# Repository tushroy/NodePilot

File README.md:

# NodePilot – CM108-Based AllStarLink Radio Interface  
NodePilot is a compact, reliable, and isolated **AllStarLink radio interface** based on the CM108 audio USB chipset by **S21TIP**.

This project was designed for both personal use and small-scale production, with a focus on audio quality, RF robustness, and hardware protection.

Channel Driver to used with ASL3: Simpleusb

The complete KiCad schematic, PCB (Work-in-progress), and design files are publicly available under the **CC-BY-SA-4.0** license.

Notes: If you are using buck converters to power Raspberry Pi boards, make sure the switching frequency is greater than 1 MHz for clean audio interfacing. Low-cost converters are often a significant source of RFI, although this circuit can eliminate most of it.

---

## 🔧 Features

✔️ CM108 Frontend Protection  
✔️ Full Audio Isolation  
✔️ Compact & Modular  
✔️ Open Hardware  

---

## 𖤓 Schematic

---

## 📐 PCB

---

---

## 📜 License

This project is released under the **Creative Commons Attribution-ShareAlike 4.0 International (CC-BY-SA-4.0)** license.  
You are free to remix, adapt, and build upon the design, even commercially, as long as you credit the author and share derivative works under the same license.

---

## 📡 Author  
**Tushar Roy – S21TIP**

If you improve the design or build your own version, feel free to open an Issue or Pull Request!

---

## 🌐 Links

### 🔗 QRZ Page  
https://www.qrz.com/db/S21TIP

### 🔗 Radiosanda FB Page  
https://www.facebook.com/share/1FPaPZSuz1/

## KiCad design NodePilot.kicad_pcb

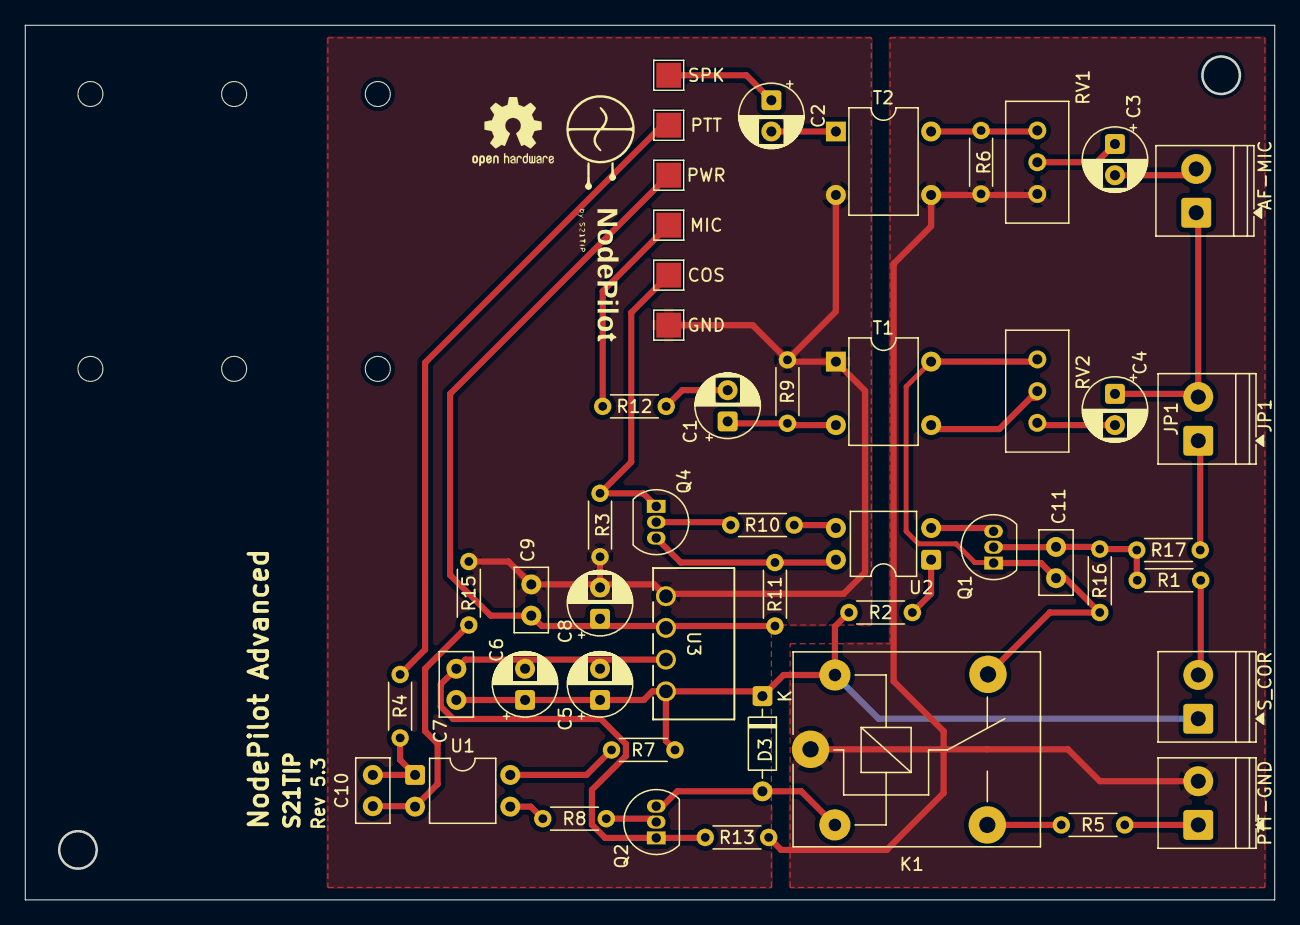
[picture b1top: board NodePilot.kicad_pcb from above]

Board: 2 copper layers, 99.9 x 69.9 mm, 40 parts (0 on the bottom side), 29 nets.

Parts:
C1, C3, C4, C6: 4.7 uf; CP_Radial_D5.0mm_P2.50mm
C2, C5, C8: 10 uf; CP_Radial_D5.0mm_P2.50mm
C7, C9: 104; C_Disc_D5.0mm_W2.5mm_P2.50mm
C10, C11: 103; C_Disc_D5.0mm_W2.5mm_P2.50mm
D3: 1N5817; D_DO-35_SOD27_P7.62mm_Horizontal
JP1: JP1; TerminalBlock_Phoenix_PT-1,5-2-3.5-H_1x02_P3.50mm_Horizontal
K1: SRD-05VDC-SL-C; Relay_SPDT_SANYOU_SRD_Series_Form_C
Q1, Q4: 2N3904; TO-92_Inline
Q2: 2N2222; TO-92_Inline
R1: 2.2k ohm; R_Axial_DIN0204_L3.6mm_D1.6mm_P5.08mm_Horizontal
R2, R4, R6, R9: 680 ohm; R_Axial_DIN0204_L3.6mm_D1.6mm_P5.08mm_Horizontal
R3, R8, R10, R11: 1k ohm; R_Axial_DIN0204_L3.6mm_D1.6mm_P5.08mm_Horizontal
R5: 2.2 ohm; R_Axial_DIN0204_L3.6mm_D1.6mm_P5.08mm_Horizontal
R7: 220 ohm; R_Axial_DIN0204_L3.6mm_D1.6mm_P5.08mm_Horizontal
R12, R17: 10k ohm; R_Axial_DIN0204_L3.6mm_D1.6mm_P5.08mm_Horizontal
R13, R15: 0 ohm; R_Axial_DIN0204_L3.6mm_D1.6mm_P5.08mm_Horizontal
R16: 100k ohm; R_Axial_DIN0204_L3.6mm_D1.6mm_P5.08mm_Horizontal
RV1, RV2: 10k; Potentiometer_Bourns_3296W_Vertical
T1, T2: 1:1 600R; Diode_Bridge_DIP-4_W7.62mm_P5.08mm
U1, U2: PC817; DIP-4_W7.62mm
U3: B0505S-1WR2; B0505S-1WR2_MNS

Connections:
GROUND: C8.2, C9.1, R3.2, R9.1, R15.1, T1.1 (AA), T2.2 (AB), U3.1 (GND)
unnamed: C1.2, R12.2
unnamed: C3.1, RV1.2
unnamed: C4.2, RV2.1
unnamed: C10.1, R15.2, U1.2
unnamed: C10.2, R4.2, U1.1
unnamed: D3.2 (A), K1.2, Q2.3 (C)
unnamed: C5.1, C6.1, C7.1, D3.1 (K), K1.5, R2.2, R7.2, U3.4 (+VO)
unnamed: JP1.1 (A), R17.1
unnamed: K1.3, R5.1
unnamed: C11.1, Q1.2 (B), R1.1, R16.1, R17.2
unnamed: Q1.3 (C), U2.2
unnamed: C11.2, K1.4, Q1.1 (E), R16.2, RV2.3, T1.4 (SB)
unnamed: Q2.2 (B), R8.2
unnamed: C5.2, C6.2, C7.2, Q2.1 (E), R13.1, U3.3 (0V)
unnamed: Q4.2 (B), R10.1
unnamed: Q4.3 (C), R11.1, U2.4
unnamed: R2.1, U2.1
unnamed: R7.1, U1.4
unnamed: R8.1, U1.3
unnamed: R10.2, U2.3
unnamed: C1.1, R9.2, T1.2 (AB)
unnamed: RV2.2, T1.3 (SA)
unnamed: C2.2, T2.1 (AA)
unnamed: R6.1, RV1.3, T2.4 (SB)
RIGAF: C4.1, JP1.2 (B)
RIGGND: K1.1, R6.2, R13.2, RV1.1, T2.3 (SA)
USBPWR: C8.1, C9.2, R11.2, U3.2 (VIN)
VOLDN: Q4.1 (E), R3.1

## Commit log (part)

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2025-11-30 init2
2025-12-08 Rename license.txt to LICENSE
2025-12-12 .gitignore house-keeping
2025-12-12 update gitignore
2025-12-13 version 3.2
2025-12-16 readme update
2025-12-17 drafted for Relay coil + audio ground coupling #2
2025-12-17 draft 2
2025-12-18 fix for issue #2
2025-12-27 version 5.1
2026-01-24 Remix v1.0
2026-01-24 NodePilot Remix v1.0
2026-01-29 cosmetic change
2026-02-19 ver 1.1
2026-02-23 audio stability
2026-06-21 kicad 10
2026-06-28 3904 load
